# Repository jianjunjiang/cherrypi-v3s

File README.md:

# cherrypi-v3s
Cherry PI Based On Allwinner V3S Chip

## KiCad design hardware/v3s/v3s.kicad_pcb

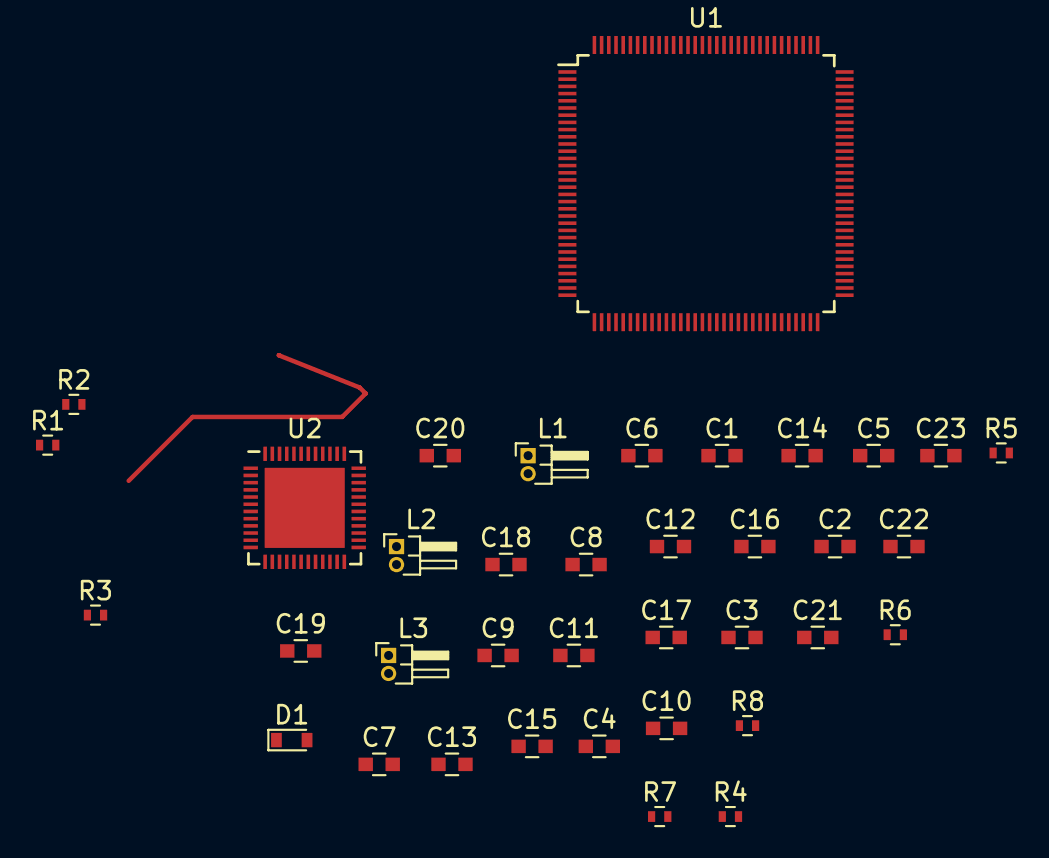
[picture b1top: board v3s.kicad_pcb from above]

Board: 2 copper layers, 37 parts (0 on the bottom side), 26 nets.

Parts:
C1, C2, C3, C9, C10, C11, C15, C17, C18, C21, C23: 10uF; C_0603
C4, C5, C22: 1uF; C_0603
C6, C8, C12, C13, C14, C16: 4.7uF; C_0603
C7: 104; C_0603
C19, C20: 10uF/NC; C_0603
D1: CHGLED; D_0603
L1, L2, L3: 4.7uH; Pin_Header_Angled_1x02_Pitch1.00mm
R1, R2, R3: R; R_0402
R4: 100R; R_0402
R5: 1K; R_0402
R6: 200K; R_0402
R7: 47K; R_0402
R8: 30mR; R_0402
U1: V3S; LQFP-128_14x14mm_Pitch0.4mm
U2: AXP203; UQFN-48-1EP_6x6mm_Pitch0.4mm

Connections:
/cpu/VBAT: U1.65, U1.66
/power/ACIN: C2.1, U2.32, U2.33
/power/DCDC2: C17.1, C19.1, L1.2, U2.10
/power/LDO1: C12.2, U2.28
/power/LDO2: C13.2, U2.12
/power/LDO3: C14.2, U2.41
/power/LDO4: C16.2, U2.11
/power/PS: C1.1, C6.1, C7.2, C8.2, C9.2, C10.2, R5.2, U2.7, U2.14, U2.21, U2.29, U2.34, U2.35, U2.44
/power/RESET: R7.2, U2.25
/power/USBVBUS: C3.1, U2.31
/power/VBAT: C22.1, C23.1, R8.1, U2.38, U2.39, U2.42, U2.43
DCDC3: C11.2, C15.2, C18.1, C20.1, L2.2, R1.2, R2.2, R3.2, U1.68, U2.13, U2.17, U2.40
GND: C1.2, C2.2, C3.2, C4.2, C5.2, C6.2, C7.1, C8.1, C11.1, C12.1, C13.1, C14.1, C15.1, C16.1, C21.2, C23.2, R4.2, R6.2, U2.22, U2.46
unnamed: C4.1, U2.26
unnamed: C5.1, U2.24
unnamed: C10.1, C18.2, C20.2, U2.16
unnamed: C9.1, C17.2, C19.2, U2.9
unnamed: C21.1, C22.2, L3.2, R8.2
unnamed: D1.1, U2.36
unnamed: D1.2, R5.1
unnamed: L1.1, U2.8
unnamed: L2.1, U2.15
unnamed: L3.1, U2.45
unnamed: R4.1, U2.37
unnamed: R6.1, U2.23
PS: R1.1, R2.1, R3.1, U1.69

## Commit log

2017-12-23 working on v3s
2017-12-25 add axp203 datasheet
2017-12-26 working on ...
2018-01-05 working on v3s ...
